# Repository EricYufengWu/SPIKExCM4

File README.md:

## Raspberry Pi CM4 Carrier Board for LEGO SPIKE Prime

This is the final project for my Microcontrollers Programming Class. My professor gave us an open prompt which is "create something that is useful". With my previous experience and interests in designing LEGO Robotics expansion hardware, I developed a Raspberry Pi CM4 Carrier board specifically for the LEGO SPIKE Prime educational system. In short, this is a slim, self-contained add-on to the SPIKE Prime hub. It gives the educational platform a huge boost in computational power and peripheral connectivity, making it capable of running tasks such as image processing, machine learning, ROS, and more.

**Note: As of June 23rd, 2021, the camera ports unfortunately do not work on the current version (In short, I made a dumb mistake of using a different footprint for the camera connectors, which has all the pins backwards). Connecting a camera may result in the flex cable heating up or possibly some permanent damage to the CM4 board. If I ever got the chance to make another design iteration, this will be the first thing I will tackle. :(**

Youtube: https://youtu.be/AbPgGo25kjA

GrabCAD: https://grabcad.com/library/raspberry-pi-cm4-carrier-board-for-lego-spike-prime-1

For more information about this project, please checkout https://www.yufengwu.com/work/class-projects/cm4-carrier-board

## Hardware Components
To make this backpack yourself, you'll need the following hardware components:
* The carrier board PCB itself. I got the full assembly service from PCBWay, but you are welcome to find your own PCB manufacturer.
* A [Raspberry Pi Compute Module 4](https://www.raspberrypi.org/products/compute-module-4/?variant=raspberry-pi-cm4001000) **with onboard EMMC and WiFi module**. 
* Some right-angle pin headers. [Amazon Link](https://www.amazon.com/Uxcell-a14032500ux0426-Right-Header-Spacing/dp/B010ESD338/ref=sr_1_3?dchild=1&keywords=right+angle+pin+headers&qid=1624248428&sr=8-3)
* A 3.7V Lithium Polymer (LiPoly) battery with JST-PH connector in the correct polarity. It has to be both slim enough to fit inside the housing and powerful enough to handle around 1.5A nominal and 3A burst current. [Digikey Link](https://www.digikey.com/en/products/detail/jauch-quartz/LP605060JU-PCM-WIRES-70MM/9560993?s=N4IgTCBcDaIDYAcBsAGArC1ArAriAugL5A)
* A short microB male to microB male USB cable. [Digikey Link](https://www.digikey.com/en/products/detail/CAB0701/1778-1018-ND/6928231?itemSeq=364421679)
* A standard hobbyist 3D printer with PLA filament (Prusa MK3S, Prusa MINI, Ender3, etc.).

## Getting Started with the Carrier Board
1. Install the compute module onto the carrier board. Make sure to get one with EMMC memory (you probably want one with WiFi as well)

1. Close the jumper (see pic) to disable EMMC boot. 

1. Connect a microUSB data cable from the OTG port (the one closer to the corner) to your laptop.

1. Follow [this link](https://www.raspberrypi.org/documentation/hardware/computemodule/cm-emmc-flashing.md) to flash the compute module's EMMC. The spscific steps depend on your computer's operating system (see the link for details). After this, you should have an operating system of your choice installed on the compute module. 

1. To minimize its size, this board is designed to have your Pi communicate with your computer via a serial console cable. You may now follow [this link](https://learn.adafruit.com/adafruits-raspberry-pi-lesson-5-using-a-console-cable/overview) to set up the communication. As for the "Connecting the Lead" section, refer to the following picture for wiring. Specifically, you'll want the following line of text be added to the last line of config.txt, which you may found in your Pi as a mass storage device right after writing the OS onto your compute module.
    ```
    enable_uart=1
    ```

1. For thir carrier board specifically, you also might want to add the following to config.txt, since the GPIO pins for UART5 were also made available in case you want to use the console cable and UART at the same time.
    ```
    dtoverlay=uart5
    ```

1. If the TTL cable connection is successful, you may continue to set up other hardware, such as WiFi and USB, in order to release the full potential of your compute module. You may use a short microB male to microB male USB cable to connect your carriar board to a LEGO SPIKE Prime. To enable USB, add the following line to config.txt:
    ```
    dtoverlay=dwc2,dr_mode=host
    ```

1. Happy hacking!

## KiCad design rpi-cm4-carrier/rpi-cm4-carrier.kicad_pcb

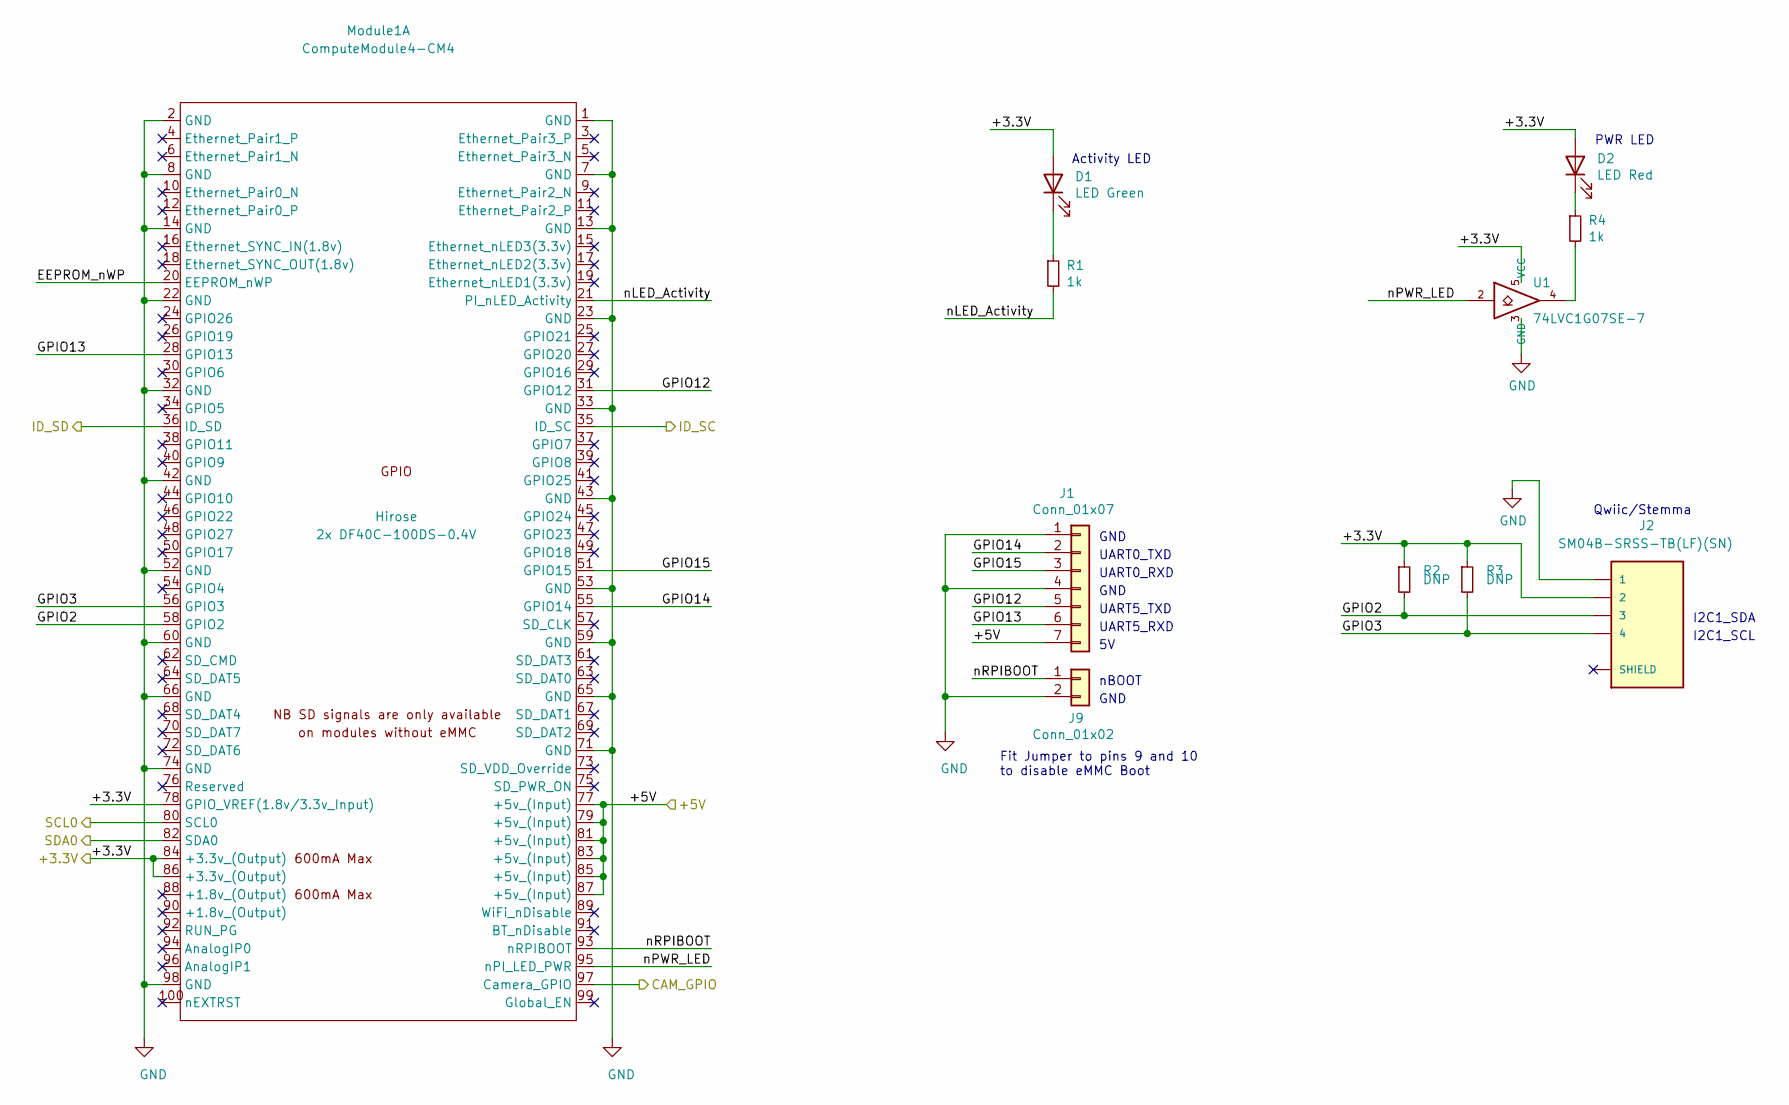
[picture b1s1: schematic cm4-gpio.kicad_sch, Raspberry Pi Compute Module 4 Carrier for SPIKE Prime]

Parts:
D1: LED Green; LED_0603_1608Metric; Part Description Green 572nm LED Indication - Discrete 2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; Digi-Key_PN 160-1478-1-ND
D2: LED Red; LED_0603_1608Metric; Part Description Red 620nm LED Indication - Discrete 2.2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; Digi-Key_PN 160-1479-1-ND
J1: Conn_01x07; PinHeader_1x07_P2.54mm_Horizontal
J2: SM04B-SRSS-TB(LF)(SN); JST_SM04B-SRSS-TB(LF)(SN); MPN SM04B-SRSS-TB(LF)(SN); Digi-Key_PN 455-1804-1-ND
J9: Conn_01x02; PinHeader_1x02_P2.54mm_Horizontal
Module1: ComputeModule4-CM4; Raspberry-Pi-4-Compute-Module; MPN 2x DF40C-100DS-0.4V; Digi-Key_PN 2x H11615CT-ND
R1, R4: 1k; R_0603_1608Metric; MPN RC0603FR-071KL; Digi-Key_PN 311-1.00KHRCT-ND
R2, R3: DNP; R_0805_2012Metric
U1: 74LVC1G07SE-7; SOT-353_SC-70-5; Part Description Buffer, Non-Inverting 1 Element 1 Bit p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; Digi-Key_PN 74LVC1G07SE-7DICT-ND

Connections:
/+3.3v: D1.2 (A), D2.2 (A), J2.2, Module1.78 (GPIO_VREF(1.8v/3.3v_Input)), Module1.84 (+3.3v_(Output)), Module1.86 (+3.3v_(Output)), R2.1, R3.1, U1.5 (VCC); also elsewhere on the board
/+5v: J1.7, Module1.77 (+5v_(Input)), Module1.79 (+5v_(Input)), Module1.81 (+5v_(Input)), Module1.83 (+5v_(Input)), Module1.85 (+5v_(Input)), Module1.87 (+5v_(Input)); also elsewhere on the board
/CM4 GPIO/EEPROM_nWP: Module1.20 (EEPROM_nWP)
/CM4 GPIO/GPIO2: J2.3, Module1.58 (GPIO2), R2.2
/CM4 GPIO/GPIO3: J2.4, Module1.56 (GPIO3), R3.2
/CM4 GPIO/GPIO12: J1.5, Module1.31 (GPIO12)
/CM4 GPIO/GPIO13: J1.6, Module1.28 (GPIO13)
/CM4 GPIO/GPIO14: J1.2, Module1.55 (GPIO14)
/CM4 GPIO/GPIO15: J1.3, Module1.51 (GPIO15)
/CM4 GPIO/nLED_Activity: Module1.21 (PI_nLED_Activity), R1.2
/CM4 GPIO/nPWR_LED: Module1.95 (nPI_LED_PWR), U1.2
/CM4 GPIO/nRPIBOOT: J9.1, Module1.93 (nRPIBOOT)
/CM4 High Speed/CAM_GPIO: Module1.97 (Camera_GPIO); also elsewhere on the board
/CM4 High Speed/ID_SC: Module1.35 (ID_SC); also elsewhere on the board
/CM4 High Speed/ID_SD: Module1.36 (ID_SD); also elsewhere on the board
/CM4 High Speed/SCL0: Module1.80 (SCL0); also elsewhere on the board
/CM4 High Speed/SDA0: Module1.82 (SDA0); also elsewhere on the board
GND: J1.1, J1.4, J2.1, J9.2, Module1.1 (GND), Module1.2 (GND), Module1.7 (GND), Module1.8 (GND), Module1.13 (GND), Module1.14 (GND), Module1.22 (GND), Module1.23 (GND), Module1.32 (GND), Module1.33 (GND), Module1.42 (GND), Module1.43 (GND), Module1.52 (GND), Module1.53 (GND), Module1.59 (GND), Module1.60 (GND), Module1.65 (GND), Module1.66 (GND), Module1.71 (GND), Module1.74 (GND), Module1.98 (GND), U1.3 (GND); also elsewhere on the board
unnamed: D1.1 (K), R1.1
unnamed: D2.1 (K), R4.1
unnamed: R4.2, U1.4

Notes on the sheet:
Fit Jumper to pins 9 and 10 to disable eMMC Boot
Activity LED
GND
UART0_TXD
UART0_RXD
UART5_TXD
UART5_RXD
nBOOT
PWR LED
Qwiic/Stemma
I2C1_SDA
I2C1_SCL

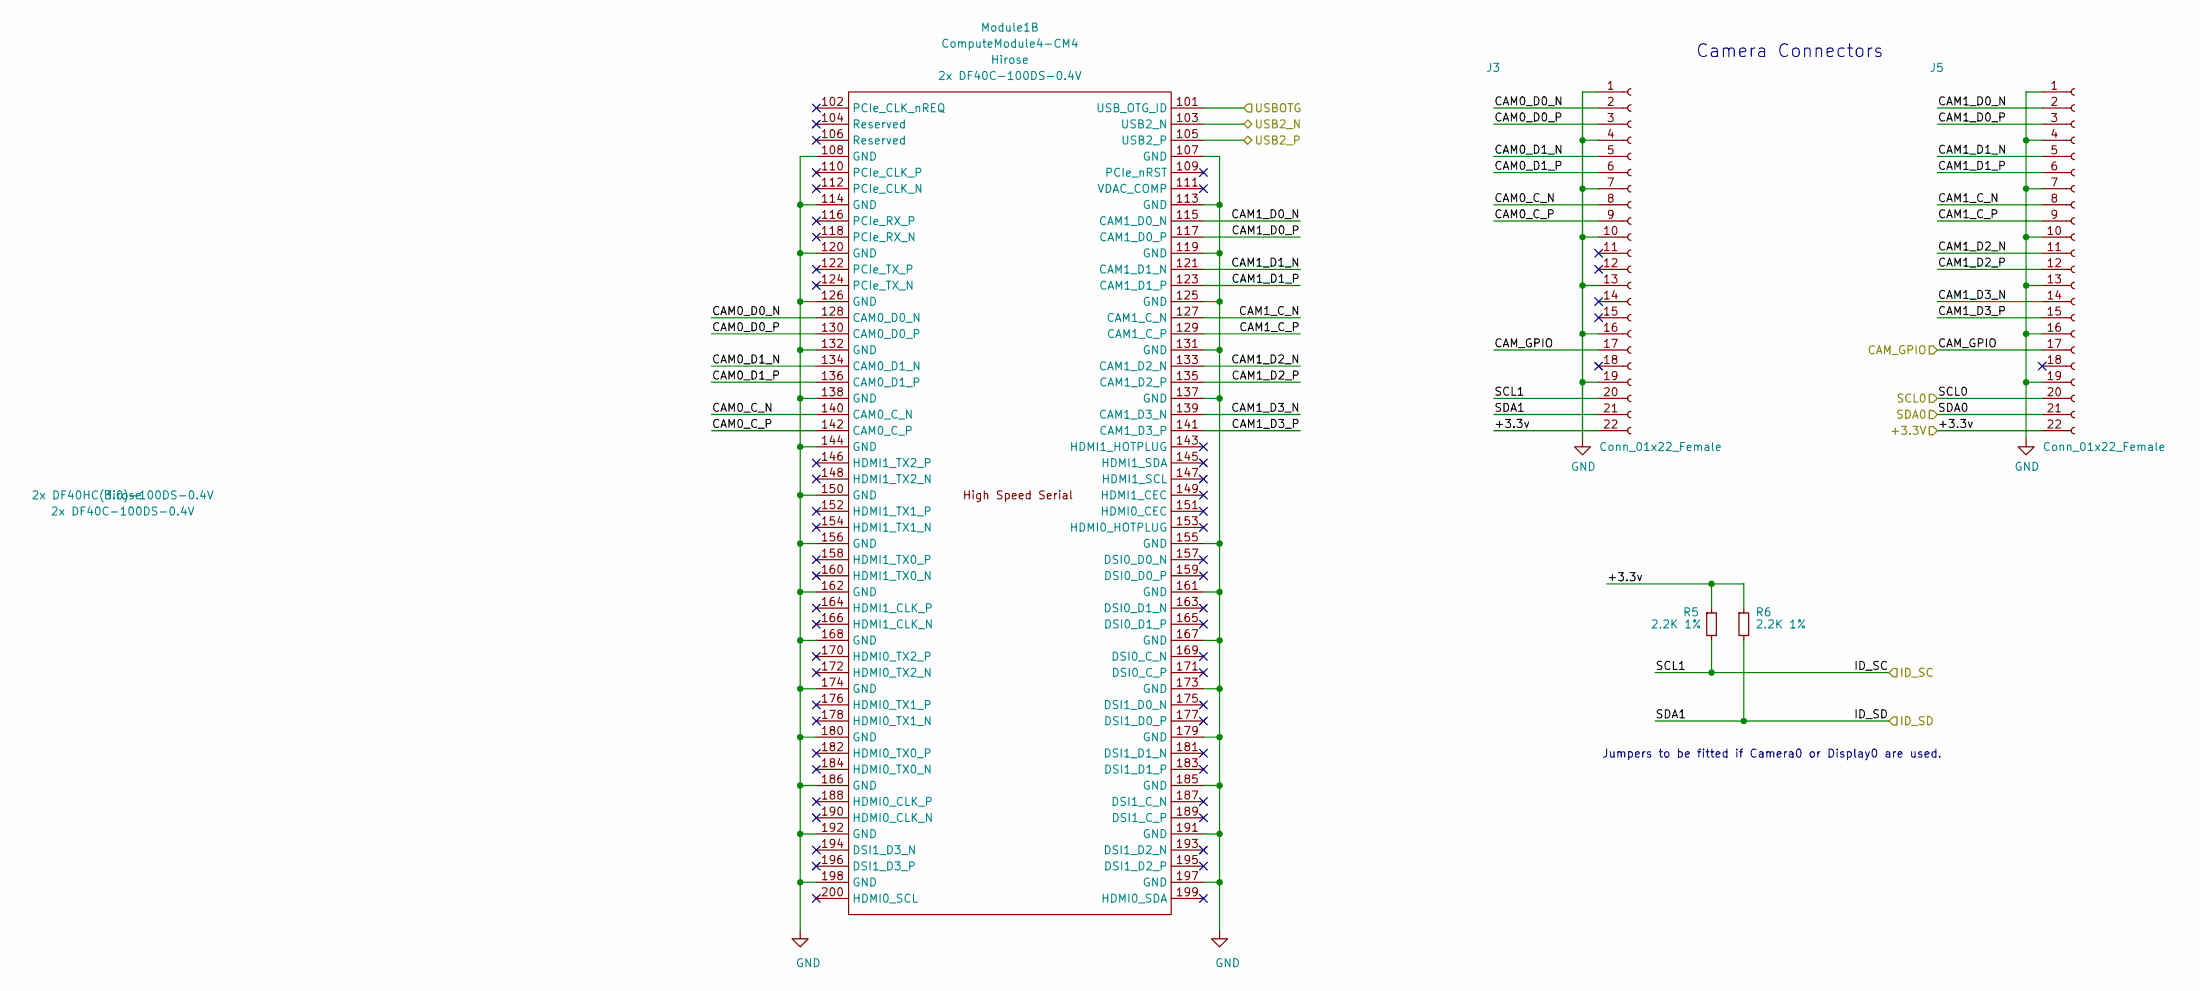
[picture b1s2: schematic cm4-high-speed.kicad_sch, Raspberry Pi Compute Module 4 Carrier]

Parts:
J3, J5: Conn_01x22_Female; Hirose_FH12-22S-0.5SH_1x22-1MP_P0.50mm_Horizontal; Part Description 22 Position FFC, FPC Connector Contacts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
Module1: ComputeModule4-CM4; Raspberry-Pi-4-Compute-Module; MPN 2x DF40C-100DS-0.4V; Digi-Key_PN 2x H11615CT-ND
R5, R6: 2.2K 1%; R_0402_1005Metric; Part Description Resistor 2.2K M1005 1% 63mW

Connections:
/+3.3v: J3.22, J5.22, R5.1, R6.1; also elsewhere on the board
/CM4 High Speed/CAM0_C_N: J3.8, Module1.140 (CAM0_C_N)
/CM4 High Speed/CAM0_C_P: J3.9, Module1.142 (CAM0_C_P)
/CM4 High Speed/CAM0_D0_N: J3.2, Module1.128 (CAM0_D0_N)
/CM4 High Speed/CAM0_D0_P: J3.3, Module1.130 (CAM0_D0_P)
/CM4 High Speed/CAM0_D1_N: J3.5, Module1.134 (CAM0_D1_N)
/CM4 High Speed/CAM0_D1_P: J3.6, Module1.136 (CAM0_D1_P)
/CM4 High Speed/CAM1_C_N: J5.8, Module1.127 (CAM1_C_N)
/CM4 High Speed/CAM1_C_P: J5.9, Module1.129 (CAM1_C_P)
/CM4 High Speed/CAM1_D0_N: J5.2, Module1.115 (CAM1_D0_N)
/CM4 High Speed/CAM1_D0_P: J5.3, Module1.117 (CAM1_D0_P)
/CM4 High Speed/CAM1_D1_N: J5.5, Module1.121 (CAM1_D1_N)
/CM4 High Speed/CAM1_D1_P: J5.6, Module1.123 (CAM1_D1_P)
/CM4 High Speed/CAM1_D2_N: J5.11, Module1.133 (CAM1_D2_N)
/CM4 High Speed/CAM1_D2_P: J5.12, Module1.135 (CAM1_D2_P)
/CM4 High Speed/CAM1_D3_N: J5.14, Module1.139 (CAM1_D3_N)
/CM4 High Speed/CAM1_D3_P: J5.15, Module1.141 (CAM1_D3_P)
/CM4 High Speed/CAM_GPIO: J3.17, J5.17; also elsewhere on the board
/CM4 High Speed/ID_SC: J3.20, R5.2; also elsewhere on the board
/CM4 High Speed/ID_SD: J3.21, R6.2; also elsewhere on the board
/CM4 High Speed/SCL0: J5.20; also elsewhere on the board
/CM4 High Speed/SDA0: J5.21; also elsewhere on the board
/CM4 High Speed/USB2_N: Module1.103 (USB2_N); also elsewhere on the board
/CM4 High Speed/USB2_P: Module1.105 (USB2_P); also elsewhere on the board
/CM4 High Speed/USBOTG: Module1.101 (USB_OTG_ID); also elsewhere on the board
GND: J3.1, J3.4, J3.7, J3.10, J3.13, J3.16, J3.19, J5.1, J5.4, J5.7, J5.10, J5.13, J5.16, J5.19, Module1.107 (GND), Module1.108 (GND), Module1.113 (GND), Module1.114 (GND), Module1.119 (GND), Module1.120 (GND), Module1.125 (GND), Module1.126 (GND), Module1.131 (GND), Module1.132 (GND), Module1.137 (GND), Module1.138 (GND), Module1.144 (GND), Module1.150 (GND), Module1.155 (GND), Module1.156 (GND), Module1.161 (GND), Module1.162 (GND), Module1.167 (GND), Module1.168 (GND), Module1.173 (GND), Module1.174 (GND), Module1.179 (GND), Module1.180 (GND), Module1.185 (GND), Module1.186 (GND), Module1.191 (GND), Module1.192 (GND), Module1.197 (GND), Module1.198 (GND); also elsewhere on the board

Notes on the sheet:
Camera Connectors
Jumpers to be fitted if Camera0 or Display0 are used.

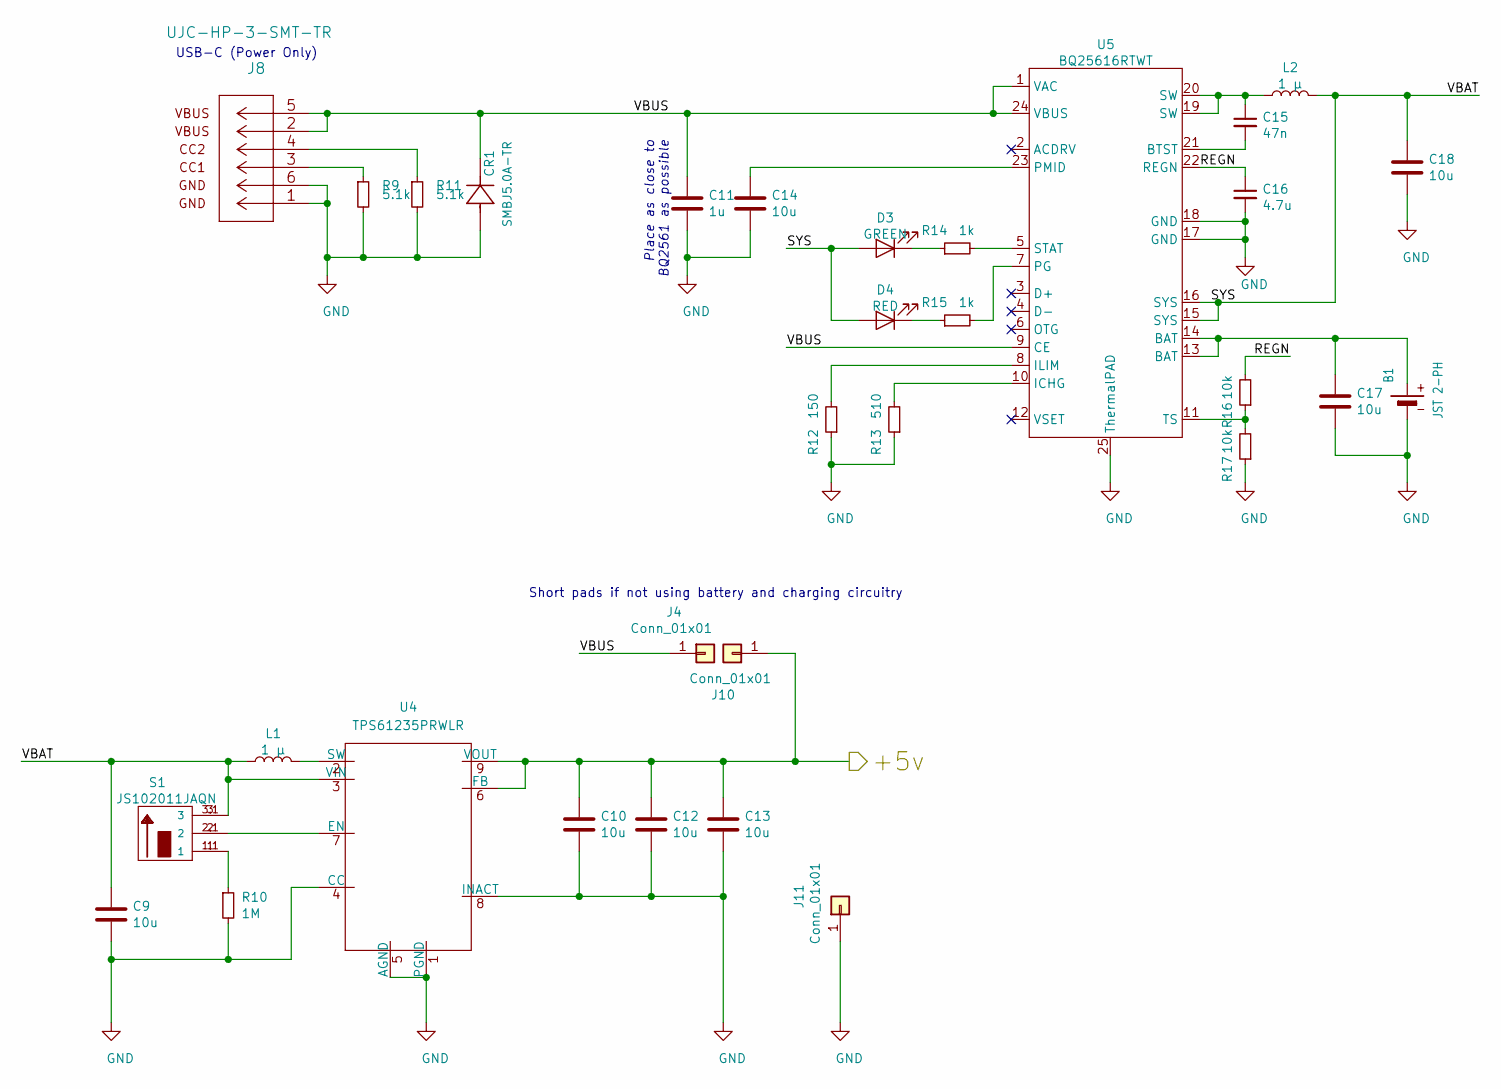
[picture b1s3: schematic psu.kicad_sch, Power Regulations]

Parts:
B1: JST 2-PH; JST_PH_S2B-PH-SM4-TB_1x02-1MP_P2.00mm_Horizontal
C9, C10, C12, C13, C14, C17, C18: 10u; C_0805_2012Metric; Part Description 10uF 10% 10V Ceramic Capacitor X7R 0805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
C11: 1u; C_0603_1608Metric; Part Description 10uF 10% 10V Ceramic Capacitor X7R 0805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
C15: 47n; C_0603_1608Metric
C16: 4.7u; C_0603_1608Metric
CR1: SMBJ5.0A-TR; MPN SMBJ5.0A-TR; Digi-Key_PN 497-3144-1-ND
D3: GREEN; LED_0603_1608Metric
D4: RED; LED_0603_1608Metric
J4, J10, J11: Conn_01x01; TestPoint_Pad_1.5x1.5mm
J8: UJC-HP-3-SMT-TR
L1, L2: 1 μ; SPM5020T-1R0M
R9, R11: 5.1k; R_0402_1005Metric; MPN RC0603FR-075K1L; Digi-Key_PN 311-5.10KHRCT-ND
R10: 1M; R_0402_1005Metric; MPN RC0603FR-071KL; Digi-Key_PN 311-1.00KHRCT-ND
R12: 150; R_0603_1608Metric; MPN RC0603FR-075K1L; Digi-Key_PN 311-5.10KHRCT-ND
R13: 510; R_0603_1608Metric; MPN RC0603FR-075K1L; Digi-Key_PN 311-5.10KHRCT-ND
R14, R15: 1k; R_0603_1608Metric; MPN RC0603FR-075K1L; Digi-Key_PN 311-5.10KHRCT-ND
R16, R17: 10k; R_0402_1005Metric; MPN RC0603FR-075K1L; Digi-Key_PN 311-5.10KHRCT-ND
S1: JS102011JAQN; SW_JS102011JAQN; PARTREV 29 June 16
U4: TPS61235PRWLR
U5: BQ25616RTWT; QFN50P400X400X80-25N

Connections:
/+5v: C10.1, C12.1, C13.1, J10.1, U4.6 (FB), U4.9 (VOUT); also elsewhere on the board
/PSUs/REGN: C16.1, R16.2, U5.22 (REGN)
/PSUs/SYS: C9.1, C18.1, D3.2 (A), D4.2 (A), L1.1, L2.2, S1.3, S1.3.1 (3), U4.3 (VIN), U5.15 (SYS), U5.16 (SYS)
/PSUs/VBUS: C11.1, CR1.1, J4.1, J8.2, J8.5, U5.1 (VAC), U5.9 (CE), U5.24 (VBUS)
GND: B1.1 (-), C9.2, C10.2, C11.2, C12.2, C13.2, C14.2, C16.2, C17.2, C18.2, CR1.2, J8.1, J8.6, J11.1, R9.2, R10.2, R11.2, R12.1, R13.1, R17.1, U4.1 (PGND), U4.4 (CC), U4.5 (AGND), U4.8 (INACT), U5.17 (GND), U5.18 (GND), U5.25 (ThermalPAD); also elsewhere on the board
unnamed: B1.2 (+), C17.1, U5.13 (BAT), U5.14 (BAT)
unnamed: C14.1, U5.23 (PMID)
unnamed: C15.1, L2.1, U5.19 (SW), U5.20 (SW)
unnamed: C15.2, U5.21 (BTST)
unnamed: D3.1 (K), R14.1
unnamed: D4.1 (K), R15.1
unnamed: J8.3, R9.1
unnamed: J8.4, R11.1
unnamed: L1.2, U4.2 (SW)
unnamed: R10.1, S1.1, S1.1.1 (1)
unnamed: R12.2, U5.8 (ILIM)
unnamed: R13.2, U5.10 (ICHG)
unnamed: R14.2, U5.5 (STAT)
unnamed: R15.2, U5.7 (PG)
unnamed: R16.1, R17.2, U5.11 (TS)
unnamed: S1.2, S1.2.1 (2), U4.7 (EN)

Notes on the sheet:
USB-C (Power Only)
Place as close to BQ2561 as possible
Short pads if not using battery and charging circuitry

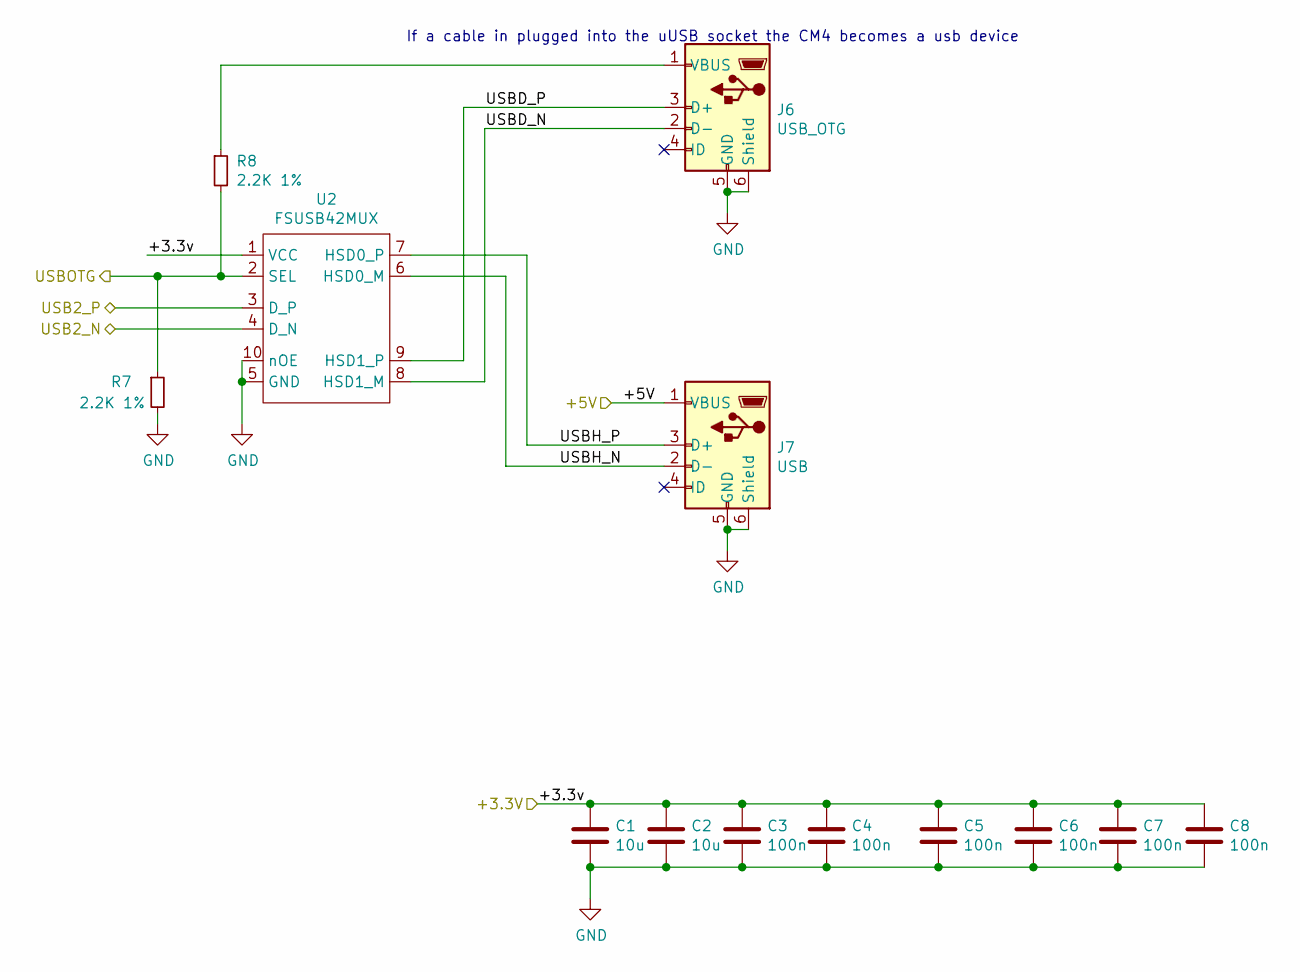
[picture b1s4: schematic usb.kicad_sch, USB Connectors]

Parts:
C1, C2: 10u; C_0805_2012Metric; Part Description 10uF 10% 10V Ceramic Capacitor X7R 0805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
C3, C4, C5, C6, C7, C8: 100n; C_0402_1005Metric; Part Description 0.1uF 10% 16V Ceramic Capacitor X7R 040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
J6: USB_OTG; USB_Micro-B_Molex-105017-0001; Part Description USB - micro B USB 2.0 Receptacle Connec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
J7: USB; USB_Micro-B_Molex-105017-0001; Part Description USB - micro B USB 2.0 Receptacle Connec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
R7, R8: 2.2K 1%; R_0402_1005Metric; Part Description Resistor 2.2K M1005 1% 63mW
U2: FSUSB42MUX; MSOP-10_3x3mm_P0.5mm; Part Description USB Switch IC 1 Channel 10-MSOP

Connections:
/+3.3v: C1.1, C2.1, C3.1, C4.1, C5.1, C6.1, C7.1, C8.1, U2.1 (VCC); also elsewhere on the board
/+5v: J7.1 (VBUS); also elsewhere on the board
/CM4 High Speed/USB2_N: U2.4 (D_N); also elsewhere on the board
/CM4 High Speed/USB2_P: U2.3 (D_P); also elsewhere on the board
/CM4 High Speed/USBOTG: R7.1, R8.2, U2.2 (SEL); also elsewhere on the board
/USB/USBD_N: J6.2 (D-), U2.8 (HSD1_M)
/USB/USBD_P: J6.3 (D+), U2.9 (HSD1_P)
/USB/USBH_N: J7.2 (D-), U2.6 (HSD0_M)
/USB/USBH_P: J7.3 (D+), U2.7 (HSD0_P)
GND: C1.2, C2.2, C3.2, C4.2, C5.2, C6.2, C7.2, C8.2, J6.5 (GND), J6.6 (Shield), J7.5 (GND), J7.6 (Shield), R7.2, U2.5 (GND), U2.10 (nOE); also elsewhere on the board
unnamed: J6.1 (VBUS), R8.1

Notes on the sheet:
If a cable in plugged into the uUSB socket the CM4 becomes a usb device

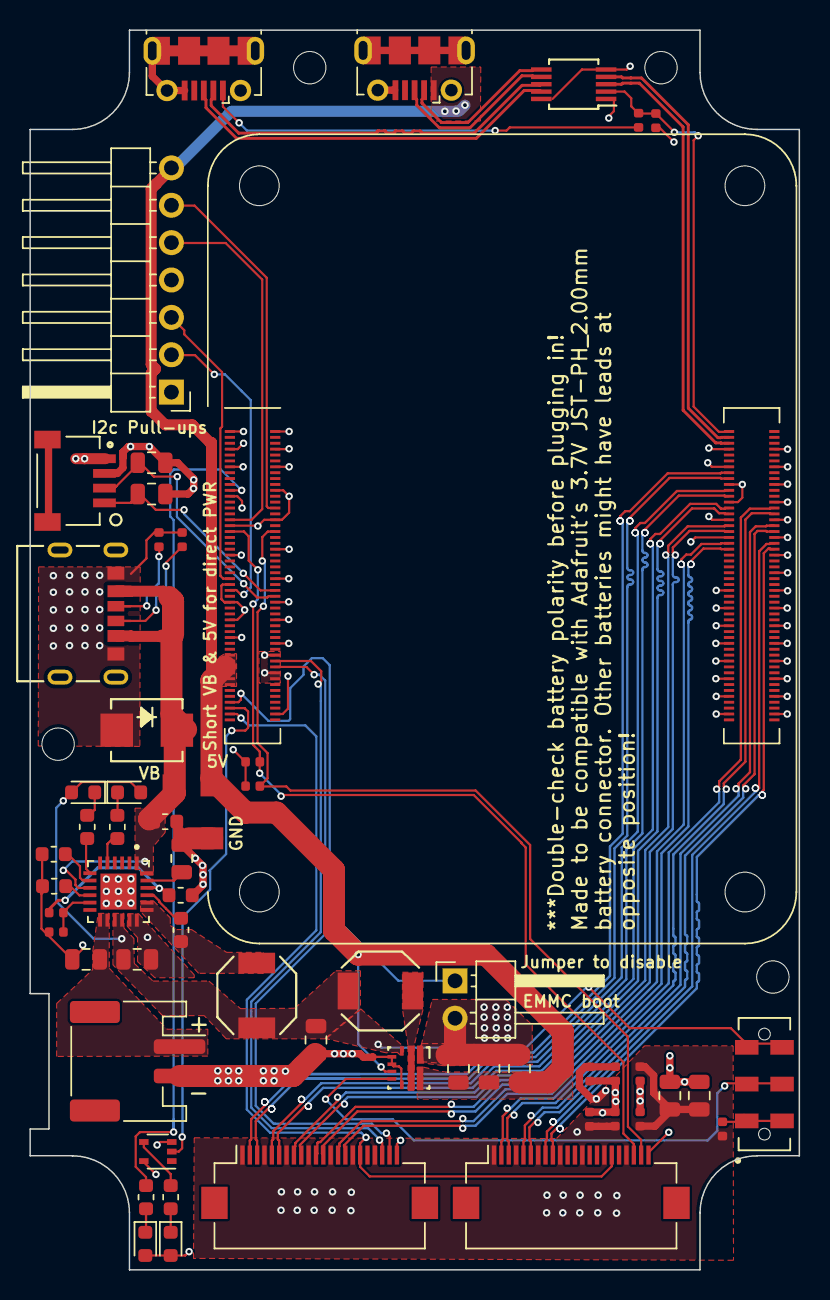
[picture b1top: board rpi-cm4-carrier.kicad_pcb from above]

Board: 4 copper layers, 52.3 x 84.2 mm, 60 parts (0 on the bottom side), 63 nets.

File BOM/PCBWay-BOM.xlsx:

|  |  | xxxx xxxx xxxxx xxPCS BOM (Sample Bill of Materials)
Item # | *Designator | *Qty | Manufacturer | *Mfg Part # | Description / Value | *Package/Footprint | Type | Your Instructions / Notes
1 | B1 | 1 | JST Sales America Inc. | S2B-PH-SM4-TB(LF)(SN) | Connector Header Surface Mount, Right Angle 2 position 0.079" (2.00mm) | 2.00mm pitch | SMD | https://www.digikey.com/en/products/detail/jst-sales-america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
2 | C1,C2,C9,C10,C12,C13,C14,C17,C18 | 9 | Samsung Electro-Mechanics | CL21A106KPFNNWE | 10uF ±10% 10V Ceramic Capacitor X5R 0805 (2012 Metric) | 0805 | SMD | https://www.digikey.com/en/products/detail/samsung-electro-m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
3 | C3,C4,C5,C6,C7,C8 | 6 | Samsung Electro-Mechanics | CL05B104KP5NNNC | 0.1uF ±10% 10V Ceramic Capacitor X7R 0402 (1005 Metric) | 0402 | SMD | https://www.digikey.com/en/products/detail/samsung-electro-m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
4 | C11 | 1 | Samsung Electro-Mechanics | CL10B105KP8NNNC | 1uF ±10% 10V Ceramic Capacitor X7R 0603 (1608 Metric) | 0603 | SMD | https://www.digikey.com/en/products/detail/samsung-electro-m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
5 | C15 | 1 | Vishay Vitramon | VJ0603Y473JXQPW1BC | 0.047uF ±5% 10V Ceramic Capacitor X7R 0603 (1608 Metric) | 0603 | SMD | https://www.digikey.com/en/products/detail/vishay-vitramon/V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
6 | C16 | 1 | Samsung Electro-Mechanics | CL10A475KP8NNNC | 4.7uF ±10% 10V Ceramic Capacitor X5R 0603 (1608 Metric) | 0603 | SMD | https://www.digikey.com/en/products/detail/samsung-electro-m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
7 | CR1 | 1 | Diodes Incorporated | SMBJ5.0A-13-F | TVS DIODE 5V 9.2V SMB | DO-214AA, SMB | SMD | https://www.digikey.com/en/products/detail/diodes-incorporat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
8 | D1,D3 | 2 | OSRAM Opto Semiconductors Inc. | LG Q396-PS-35 | Green 573nm LED Indication - Discrete 2V 0603 (1608 Metric) | 0603 | SMD | https://www.digikey.com/en/products/detail/osram-opto-semico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
9 | D2,D4 | 2 | OSRAM Opto Semiconductors Inc. | LED RED DIFFUSED 0603 SMD | Red 630nm LED Indication - Discrete 1.8V 0603 (1608 Metric) | 0603 | SMD | https://www.digikey.com/en/products/detail/osram-opto-semico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
11 | J2 | 1 | JST Sales America Inc. | SM04B-SRSS-TB(LF)(SN) | Connector Header Surface Mount, Right Angle 4 position 0.039" (1.00mm) | 1.00mm pitch | SMD | https://www.digikey.com/en/products/detail/hirose-electric-c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
12 | J3,J5 | 2 | Hirose Electric Co Ltd | FH12-22S-0.5SH(55) | 22 Position FFC, FPC Connector Contacts, Bottom 0.020" (0.50mm) Surface Mount, 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 | 0.50mm pitch | SMD | https://www.digikey.com/en/products/detail/jst-sales-america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
13 | J6,J7 | 2 | Molex | 1050170001 | USB - micro B USB 2.0 Receptacle Connector 5 Position Surface Mount, Right Angl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 | https://www.molex.com/pdm_docs/sd/1050170001_sd.pdf | SMD | https://www.digikey.com/en/products/detail/molex/1050170001/2350832
14 | J8 | 1 | CUI Devices | UJC-HP-3-SMT-TR | USB-C (USB TYPE-C) - Power Only - Receptacle Connector 24 (6+18 Dummy) Position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 | https://www.cuidevices.com/product/resource/ujc-hp-3-smt-tr.pdf | SMD | https://www.digikey.com/en/products/detail/cui-devices/UJC-H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
15 | L1,L2 | 2 | TDK Corporation | SPM5020T-1R0M-LR | Shielded Wirewound Inductor 17.2mOhm Max Nonstandard | Nonstandard | SMD | https://www.digikey.com/en/products/detail/tdk-corporation/S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
16 | Module1 (2 pieces) | 2 | Hirose Electric Co Ltd | DF40C-100DS-0.4V(51) | 100 Position Connector Receptacle, Center Strip Contacts Surface Mount Gold | Raspberry Pi CM4 | SMD | https://www.digikey.com/en/products/detail/hirose-electric-c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
17 | R1,R4,R14,R15 | 4 | Samsung Electro-Mechanics | RC1608F102CS | RES SMD 1K OHM 1% 1/10W 0603 | 0603 | SMD | https://www.digikey.com/en/products/detail/samsung-electro-m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
18 | R2, R3 | 2 | DO NOT PLACE | DO NOT PLACE | DO NOT PLACE | 0805 | SMD | DO NOT PLACE
19 | R5,R6,R7,R8 | 4 | Samsung Electro-Mechanics | RC1005F222CS | RES SMD 2.2K OHM 1% 1/16W 0402 | 0402 | SMD | https://www.digikey.com/en/products/detail/samsung-electro-m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
20 | R9,R11 | 2 | Samsung Electro-Mechanics | RC1005F512CS | RES SMD 5.1K OHM 1% 1/16W 0402 | 0402 | SMD | https://www.digikey.com/en/products/detail/samsung-electro-m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
21 | R10 | 1 | Yageo | RC0402FR-071ML | RES SMD 1M OHM 1% 1/16W 0402 | 0402 | SMD | https://www.digikey.com/en/products/detail/yageo/RC0402FR-07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
22 | R12 | 1 | Yageo | RC0603FR-07150RL | RES SMD 150 OHM 1% 1/10W 0603 | 0603 | SMD | https://www.digikey.com/en/products/detail/yageo/RC0603FR-07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
23 | R13 | 1 | Yageo | RC0603FR-07510RL | RES SMD 510 OHM 1% 1/10W 0603 | 0603 | SMD | https://www.digikey.com/en/products/detail/yageo/RC0603FR-07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
24 | R16,R17 | 2 | Samsung Electro-Mechanics | RC1005F103CS | RES SMD 10K OHM 1% 1/16W 0402 | 0402 | SMD | https://www.digikey.com/en/products/detail/samsung-electro-m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
25 | S1 | 1 | C&K | JS102011JAQN | SWITCH SLIDE SPDT 300MA 6V | Nonstandard | SMD | https://www.digikey.com/en/products/detail/c-k/JS102011JAQN/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
26 | U1 | 1 | Diodes Incorporated | 74LVC1G07SE-7 | IC BUF NON-INVERT 5.5V SOT353 | SOT353 | SMD | https://www.digikey.com/en/products/detail/diodes-incorporat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
27 | U2 | 1 | ON Semiconductor | FSUSB42MUX | IC USB SWITCH DPDT 10MSOP | 10MSOP | SMD | https://www.digikey.com/en/products/detail/on-semiconductor/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
28 | U4 | 1 | Texas Instruments | TPS61235PRWLR | Boost Switching Regulator IC Positive Fixed 5.1V 1 Output 6.5A (Switch) 9-VFQFN | 9VQFN | SMD | https://www.digikey.com/en/products/detail/texas-instruments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
29 | U5 | 1 | Texas Instruments | BQ25616RTWT | IC BATT CHG LI-ION 1CELL 24WQFN | 24WQFN | SMD | https://www.digikey.com/en/products/detail/texas-instruments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
Need a quick and accurante quote? Need an efficient production? Please read SMT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
Click for Instructions on How to Create a BOM

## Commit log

2021-06-18 final CAD
2021-06-21 updated README instruction
2021-06-23 images
2021-06-23 README

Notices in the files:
rpi-cm4-carrier/cm4-gpio.kicad_sch:
creativecommons.org/licenses/by-sa/4.0
License: CC BY 4.0
rpi-cm4-carrier/rpi-cm4-carrier.kicad_pcb:
creativecommons.org/licenses/by/4.0
parts and their libraries:
Copyright 2016 Accelerated Designs. All rights reserved.
